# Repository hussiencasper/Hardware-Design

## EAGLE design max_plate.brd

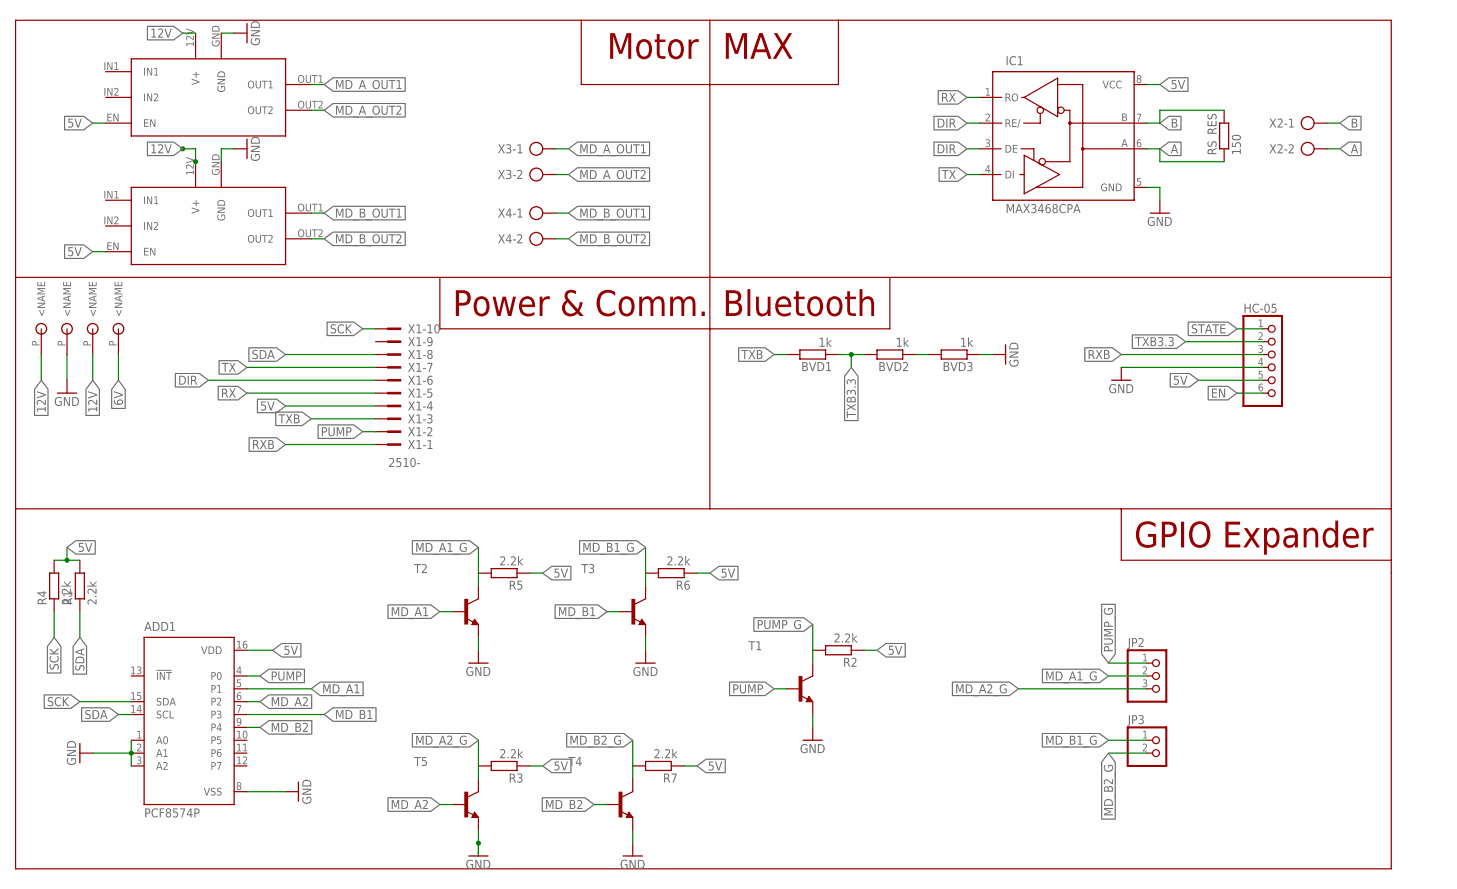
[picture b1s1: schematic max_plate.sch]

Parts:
ADD1: PCF8574P; DIL16
BVD1, BVD2, BVD3: 1k; 0207/10
HC-05: PINHD-1X6; 1X06
IC1: MAX3468CPA; DIL08
JP2: PINHD-1X3; 1X03
JP3: PINHD-1X2; 1X02
R1, R2, R3, R4, R5, R6, R7: 2.2k; 0207/10
RS_RES: 150; 0207/10
T1, T2, T3, T4, T5: -NPN-TO92; TO92
U$1, U$2, U$3, U$4: CU-SPACER
U$5, U$6: L6203-MODULE
X1: 2510-; PAK100/2500-10
X2, X3, X4: AK500/2

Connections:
5V: ADD1.16 (VDD), HC-05.5, IC1.8 (VCC), R1.2, R2.1, R3.1, R4.2, R5.1, R6.1, R7.1, U$5.EN, U$6.EN, X1.4
6V: U$4.P
12V: U$1.P, U$3.P, U$5.12V (V+), U$6.12V (V+)
A: IC1.6 (A), RS_RES.1, X2.2
B: IC1.7 (B), RS_RES.2, X2.1
DIR: IC1.2 (RE/), IC1.3 (DE), X1.6
EN: HC-05.6
GND: ADD1.1 (A0), ADD1.2 (A1), ADD1.3 (A2), ADD1.8 (VSS), BVD3.1, HC-05.4, IC1.5 (GND), T1.1 (E), T2.1 (E), T3.1 (E), T4.1 (E), T5.1 (E), U$2.P, U$5.GND, U$6.GND
MD_A1: ADD1.5 (P1), T2.2 (B)
MD_A1_G: JP2.2, R5.2, T2.3 (C)
MD_A2: ADD1.6 (P2), T5.2 (B)
MD_A2_G: JP2.3, R3.2, T5.3 (C)
MD_A_OUT1: U$5.OUT1, X3.1
MD_A_OUT2: U$5.OUT2, X3.2
MD_B1: ADD1.7 (P3), T3.2 (B)
MD_B1_G: JP3.1, R6.2, T3.3 (C)
MD_B2: ADD1.9 (P4), T4.2 (B)
MD_B2_G: JP3.2, R7.2, T4.3 (C)
MD_B_OUT1: U$6.OUT1, X4.1
MD_B_OUT2: U$6.OUT2, X4.2
unnamed: BVD2.1, BVD3.2
PUMP: ADD1.4 (P0), T1.2 (B), X1.2
PUMP_G: JP2.1, R2.2, T1.3 (C)
RX: IC1.1 (RO), X1.5
RXB: HC-05.3, X1.1
SCK: ADD1.15 (SDA), R4.1, X1.10
SDA: ADD1.14 (SCL), R1.1, X1.8
STATE: HC-05.1
TX: IC1.4 (DI), X1.7
TXB: BVD1.2, X1.3
TXB3.3: BVD1.1, BVD2.2, HC-05.2

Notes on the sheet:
MAX
Motor
Bluetooth
Power & Comm.
GPIO Expander

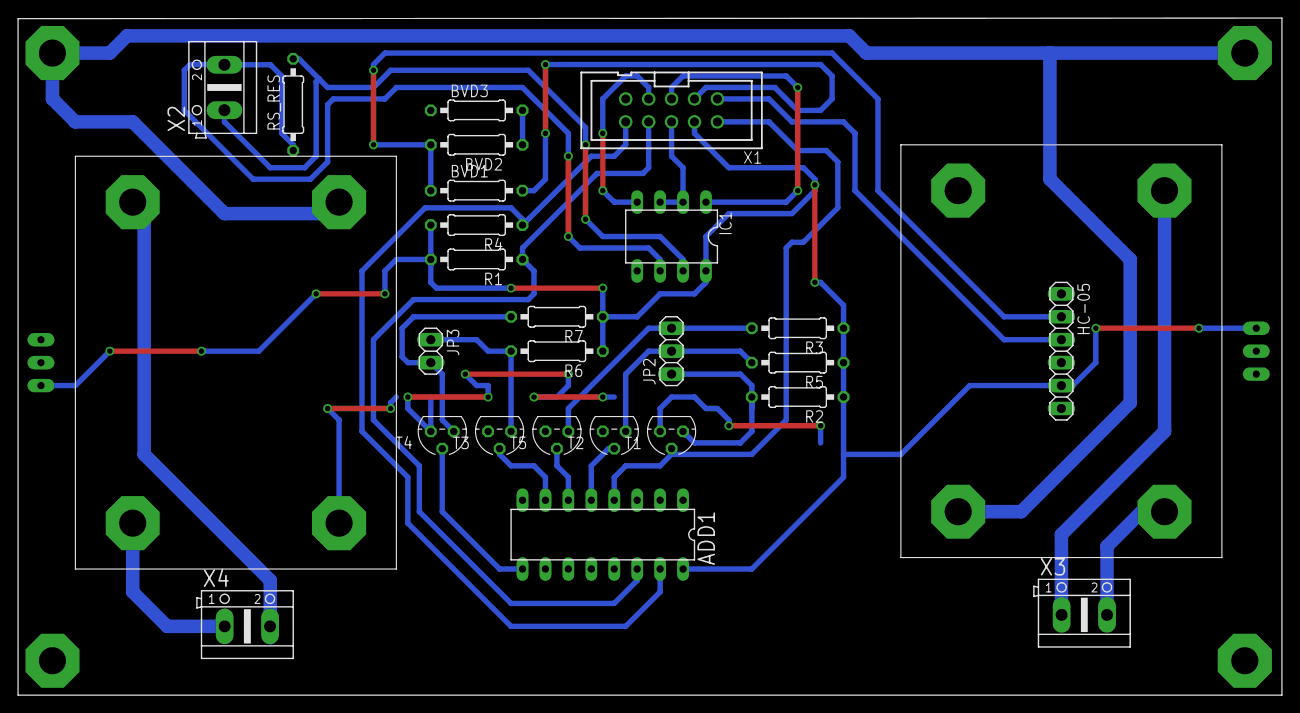
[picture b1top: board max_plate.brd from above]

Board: 2 copper layers, 140.0 x 75.0 mm, 31 parts (0 on the bottom side), 28 nets.

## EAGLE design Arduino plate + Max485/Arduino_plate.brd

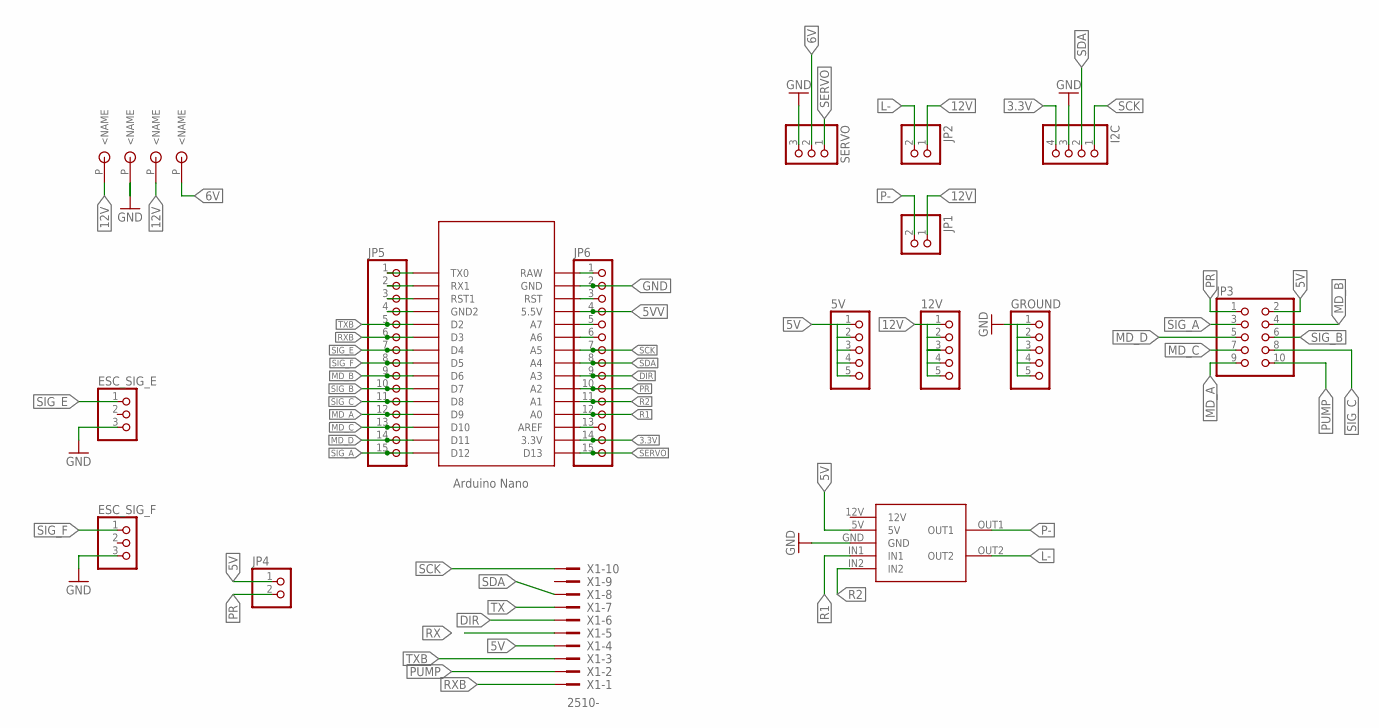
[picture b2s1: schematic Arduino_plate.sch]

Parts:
5V, 12V: PINHD-1X5; 1X05
6V, 12: CU-SPACER
ESC_SIG_E: PINHD-1X3/90; 1X03/90
ESC_SIG_F: PINHD-1X3/90; 1X03/90
GND: CU-SPACER
GROUND: PINHD-1X5; 1X05
I2C: PINHD-1X4/90; 1X04/90
JP1, JP2, JP4: PINHD-1X2/90; 1X02/90
JP3: PINHD-2X5; 2X05
JP5, JP6: PINHD-1X15; 1X15
SERVO: PINHD-1X3/90; 1X03/90
U$1: NANO
U$3: 2-RELAY-MODULE
U$4: CU-SPACER
X1: 2510-; PAK100/2500-10

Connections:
3.3V: I2C.4, JP6.14, U$1.3.3V
5V: 5V.1, 5V.2, 5V.3, 5V.4, 5V.5, JP3.2, JP4.1, U$3.5V, X1.4
5VV: JP6.4, U$1.5V (5.5V)
6V: 6V.P, SERVO.2
12V: 12.P, 12V.1, 12V.2, 12V.3, 12V.4, 12V.5, JP1.1, JP2.1, U$4.P
DIR: JP6.9, U$1.A3, X1.6
GND: ESC_SIG_E.3, ESC_SIG_F.3, GND.P, GROUND.1, GROUND.2, GROUND.3, GROUND.4, GROUND.5, I2C.3, JP6.2, SERVO.3, U$1.GND, U$3.GND
L-: JP2.2, U$3.OUT2
MD_A: JP3.9, JP5.12, U$1.D9
MD_B: JP3.4, JP5.9, U$1.D6
MD_C: JP3.7, JP5.13, U$1.D10
MD_D: JP3.5, JP5.14, U$1.D11
unnamed: JP5.3, U$1.RST1
unnamed: JP5.4, U$1.GND1 (GND2)
unnamed: JP6.1, U$1.RAW
unnamed: JP6.3, U$1.RST
unnamed: JP6.5, U$1.A7
unnamed: JP6.6, U$1.A6
unnamed: JP6.13, U$1.AREF
P-: JP1.2, U$3.OUT1
PR: JP3.1, JP4.2, JP6.10, U$1.A2
PUMP: JP3.10, X1.2
R1: JP6.12, U$1.A0, U$3.IN1
R2: JP6.11, U$1.A1, U$3.IN2
RX: JP5.2, U$1.RX1, X1.5
RXB: JP5.6, U$1.D3, X1.1
SCK: I2C.1, JP6.7, U$1.A5, X1.10
SDA: I2C.2, JP6.8, U$1.A4, X1.8
SERVO: JP6.15, SERVO.1, U$1.D13
SIG_A: JP3.3, JP5.15, U$1.D12
SIG_B: JP3.6, JP5.10, U$1.D7
SIG_C: JP3.8, JP5.11, U$1.D8
SIG_E: ESC_SIG_E.1, JP5.7, U$1.D4
SIG_F: ESC_SIG_F.1, JP5.8, U$1.D5
TX: JP5.1, U$1.TX0, X1.7
TXB: JP5.5, U$1.D2, X1.3

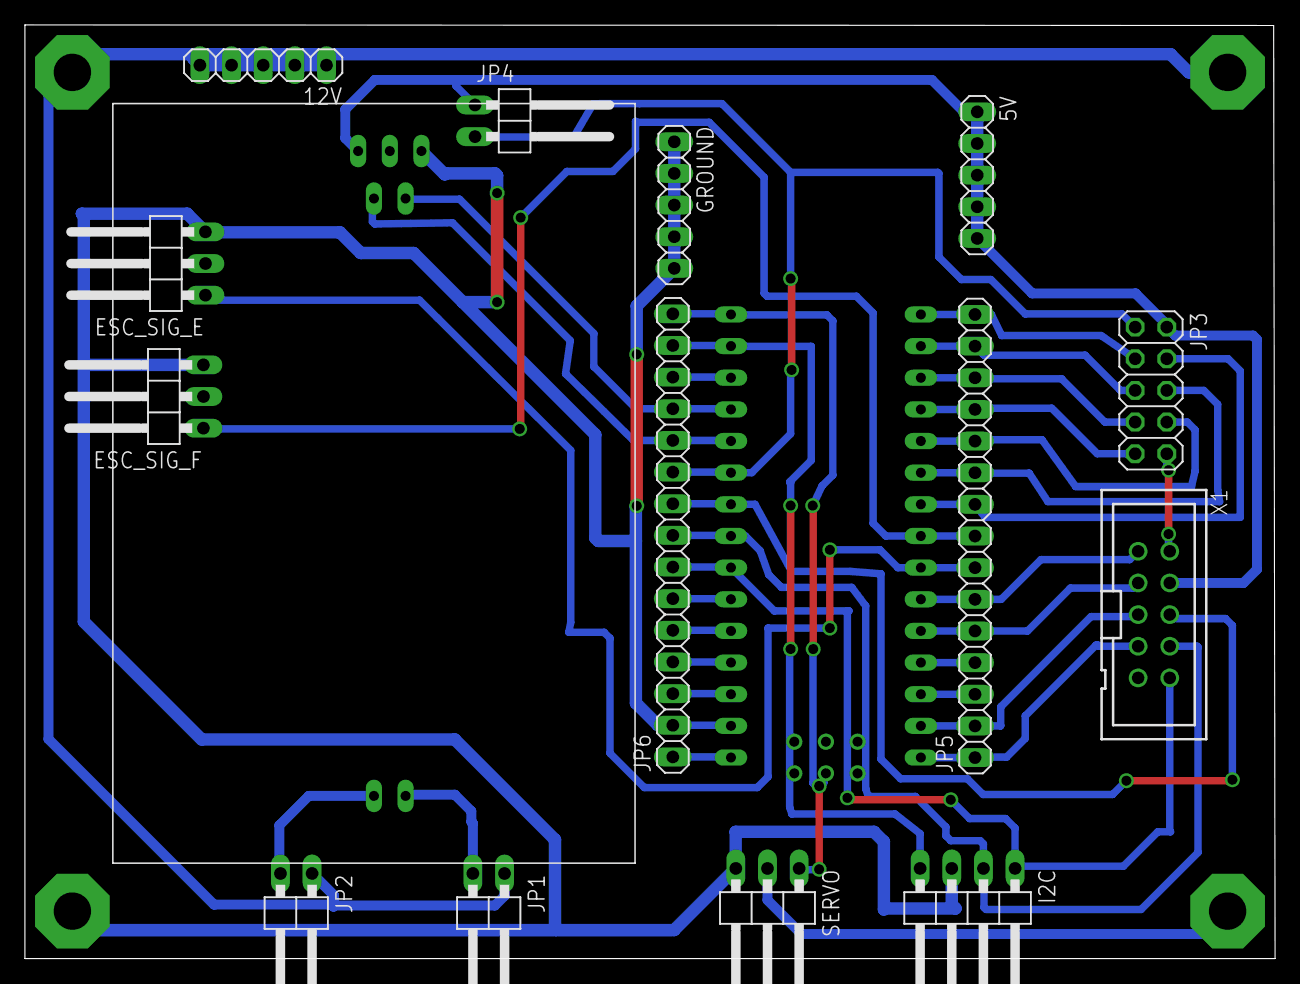
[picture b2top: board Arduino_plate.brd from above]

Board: 2 copper layers, 100.3 x 74.9 mm, 20 parts (0 on the bottom side), 36 nets.

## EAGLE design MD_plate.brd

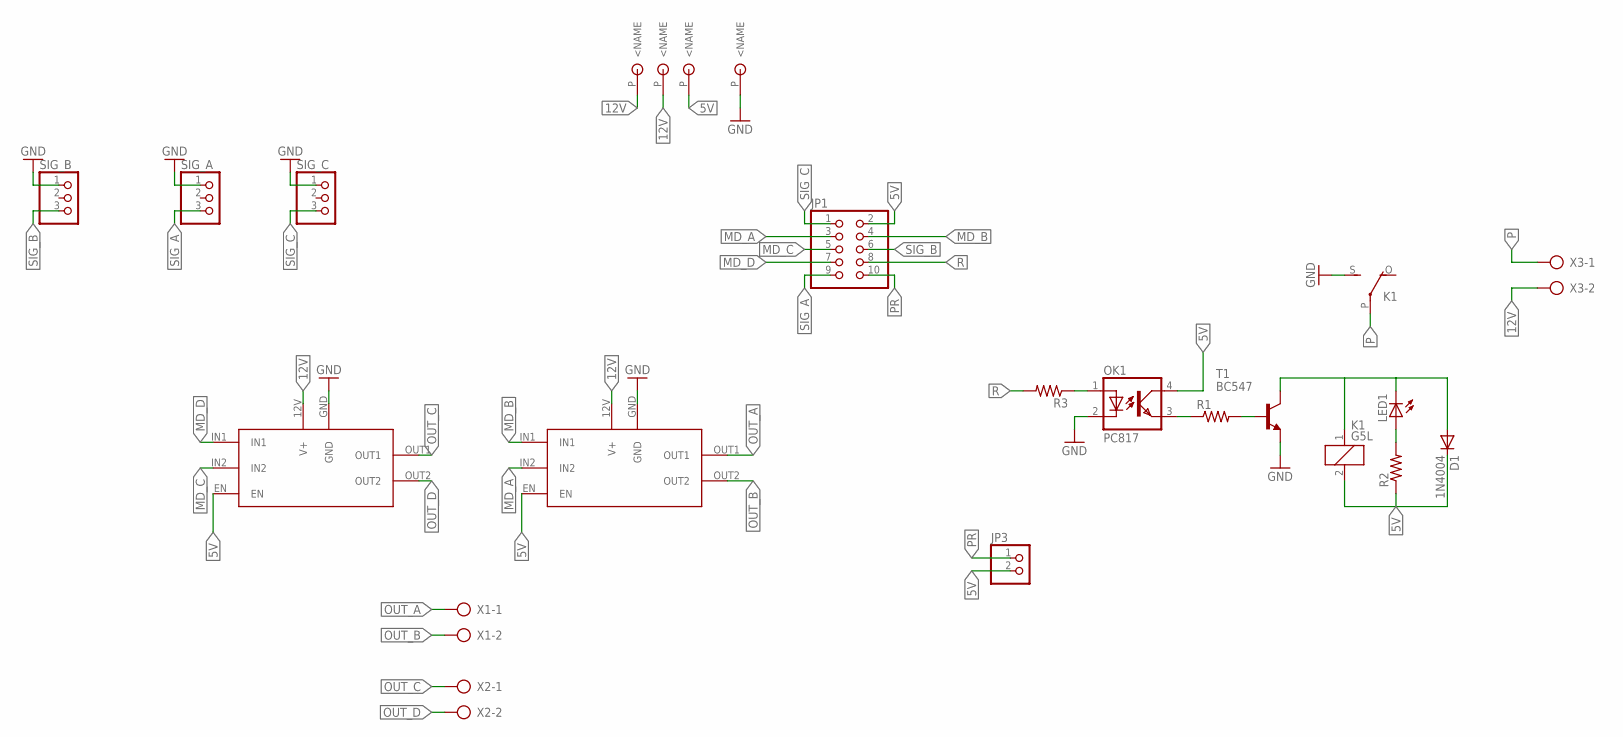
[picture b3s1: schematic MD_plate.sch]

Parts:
6, 12_A, 12_B: CU-SPACER
D1: 1N4004; DO41-10
JP1: PINHD-2X5; 2X05
JP3: PINHD-1X2; 1X02
K1: G5L; G5LE
LED1: LED3MM
OK1: PC817; DIL04
R1, R2, R3: R-US_0204/7; 0204/7
SIG_A: PINHD-1X3/90; 1X03/90
SIG_B: PINHD-1X3/90; 1X03/90
SIG_C: PINHD-1X3/90; 1X03/90
T1: BC547; TO92
U$1, U$2: L6203-MODULE
U$6: CU-SPACER
X1, X2, X3: AK500/2

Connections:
5V: 6.P, D1.C, JP1.2, JP3.2, K1.2, OK1.4 (COL), R2.1, U$1.EN, U$2.EN
12V: 12_A.P, 12_B.P, U$1.12V (V+), U$2.12V (V+), X3.2
GND: K1.S, OK1.2 (C), SIG_A.1, SIG_B.1, SIG_C.1, T1.1 (E), U$1.GND, U$2.GND, U$6.P
MD_A: JP1.3, U$2.IN2
MD_B: JP1.4, U$2.IN1
MD_C: JP1.5, U$1.IN2
MD_D: JP1.7, U$1.IN1
unnamed: OK1.3 (EMIT), R1.1
unnamed: R1.2, T1.2 (B)
unnamed: LED1.A, R2.2
unnamed: OK1.1 (A), R3.1
unnamed: D1.A, K1.1, LED1.K (C), T1.3 (C)
OUT_A: U$2.OUT1, X1.1
OUT_B: U$2.OUT2, X1.2
OUT_C: U$1.OUT1, X2.1
OUT_D: U$1.OUT2, X2.2
P: K1.P, X3.1
PR: JP1.10, JP3.1
R: JP1.8, R3.2
SIG_A: JP1.9, SIG_A.3
SIG_B: JP1.6, SIG_B.3
SIG_C: JP1.1, SIG_C.3

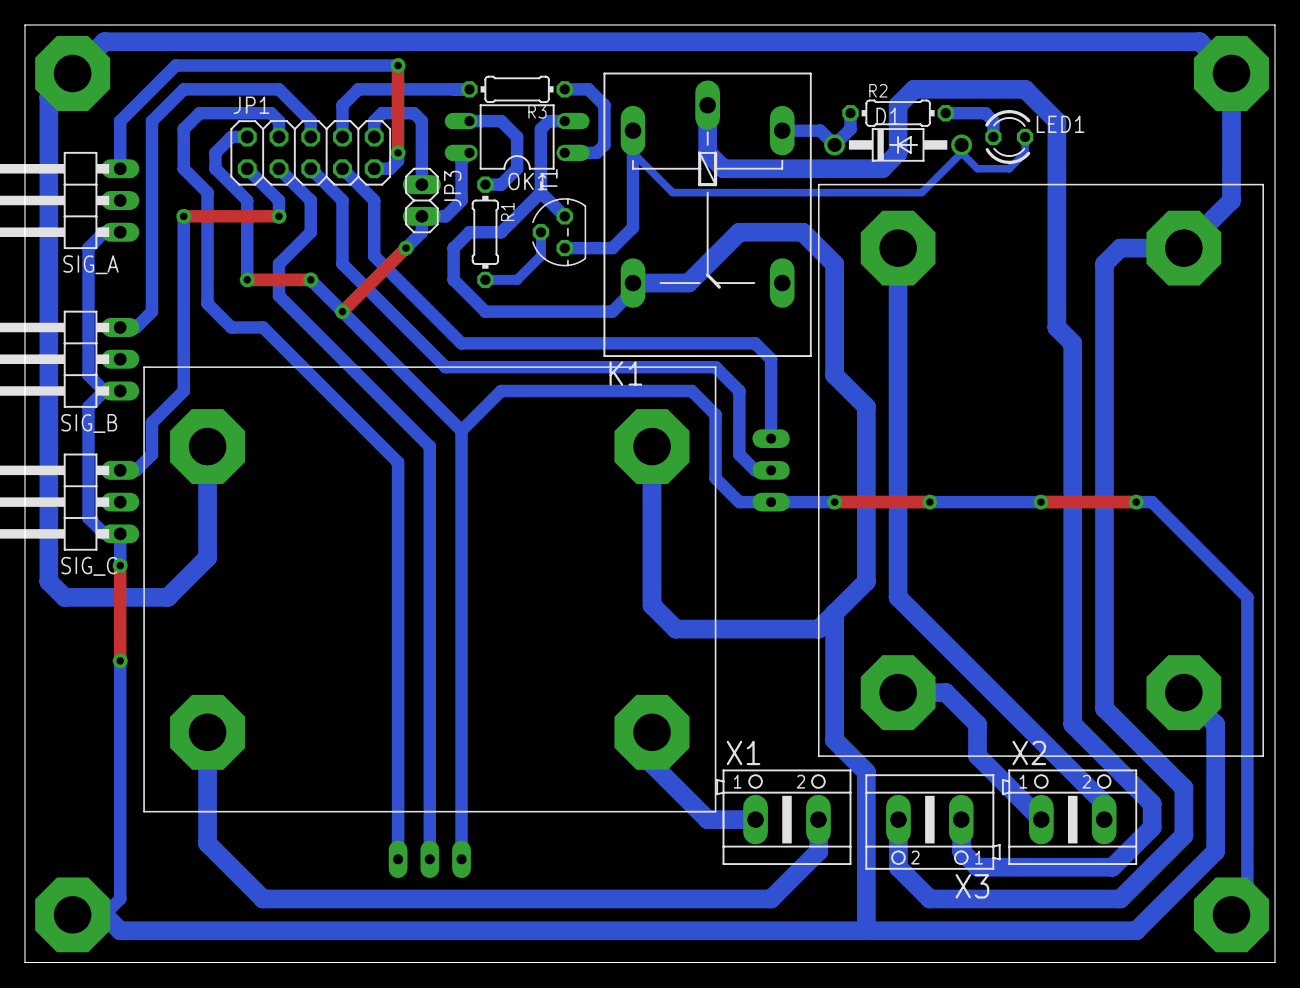
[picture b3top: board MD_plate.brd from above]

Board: 2 copper layers, 100.0 x 75.0 mm, 22 parts (0 on the bottom side), 22 nets.

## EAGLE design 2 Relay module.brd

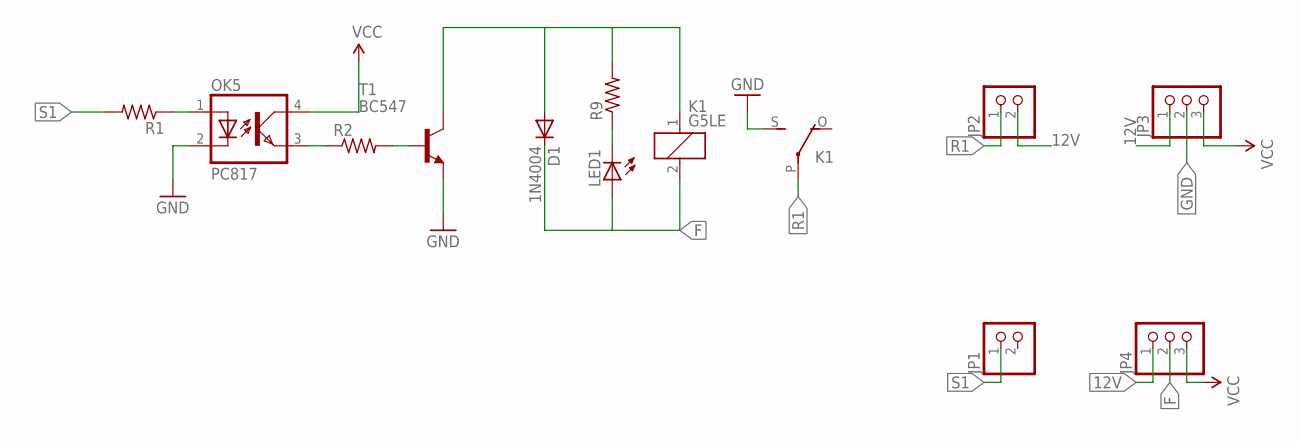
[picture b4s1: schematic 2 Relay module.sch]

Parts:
D1: 1N4004; DO41-10
JP1, JP2: PINHD-1X2; 1X02
JP3, JP4: PINHD-1X3; 1X03
K1: G5LE
LED1: LED3MM
OK5: PC817; DIL04
R1, R2, R9: R-US_0204/7; 0204/7
T1: BC547; TO92

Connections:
12V: JP2.2, JP3.1, JP4.1
F: D1.C, JP4.2, K1.2, LED1.A
GND: JP3.2, K1.S, OK5.2 (C), T1.1 (E)
unnamed: LED1.K (C), R9.1
unnamed: OK5.3 (EMIT), R2.1
unnamed: OK5.1 (A), R1.1
unnamed: R2.2, T1.2 (B)
unnamed: D1.A, K1.1, R9.2, T1.3 (C)
R1: JP2.1, K1.P
S1: JP1.1, R1.2
VCC: JP3.3, JP4.3, OK5.4 (COL)

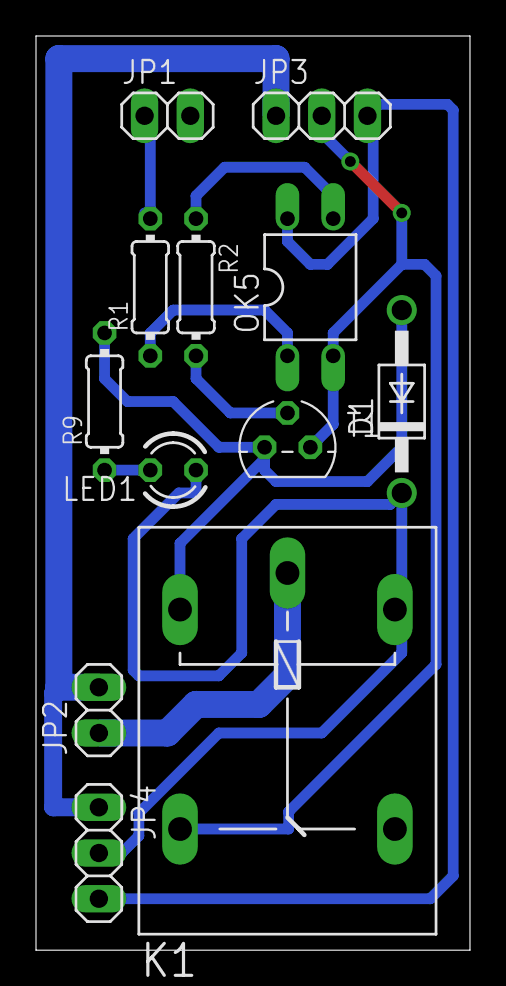
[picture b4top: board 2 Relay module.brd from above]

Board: 2 copper layers, 24.1 x 50.8 mm, 12 parts (0 on the bottom side), 11 nets.

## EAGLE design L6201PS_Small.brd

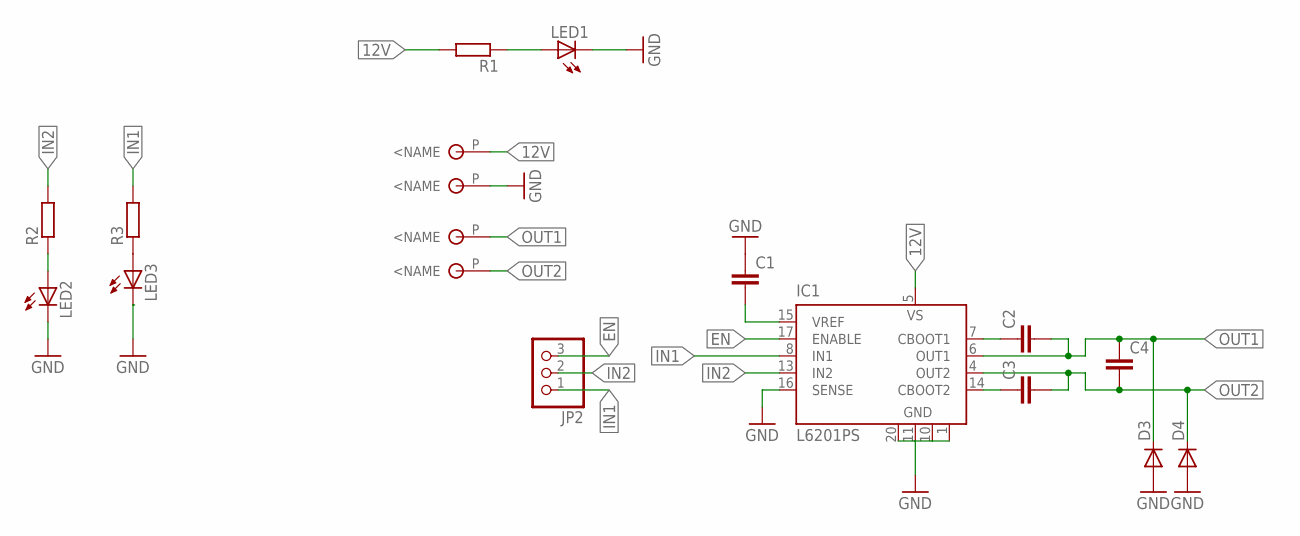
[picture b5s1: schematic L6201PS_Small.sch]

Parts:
C1, C2, C3, C4: C-EUC0603; C0603
D3, D4: DIODE-DO214AC; DO214AC
IC1: L6201PS; POWERSO-20
JP2: PINHD-1X3; 1X03
LED1, LED2, LED3: LEDSML0603; SML0603
R1, R2, R3: R-EU_R0603; R0603
U$1, U$2, U$3, U$4: CU-SPACER

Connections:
12V: IC1.5 (VS), R1.2, U$2.P
EN: IC1.17 (ENABLE), JP2.3
GND: C1.1, D3.A, D4.A, IC1.1 (GND), IC1.10 (GND), IC1.11 (GND), IC1.16 (SENSE), IC1.20 (GND), LED1.C, LED2.C, LED3.C, U$1.P
IN1: IC1.8 (IN1), JP2.1, R3.2
IN2: IC1.13 (IN2), JP2.2, R2.2
unnamed: LED3.A, R3.1
unnamed: LED1.A, R1.1
unnamed: C1.2, IC1.15 (VREF)
unnamed: C2.1, IC1.7 (CBOOT1)
unnamed: LED2.A, R2.1
unnamed: C3.1, IC1.14 (CBOOT2)
OUT1: C2.2, C4.1, D3.C, IC1.6 (OUT1), U$3.P
OUT2: C3.2, C4.2, D4.C, IC1.4 (OUT2), U$4.P

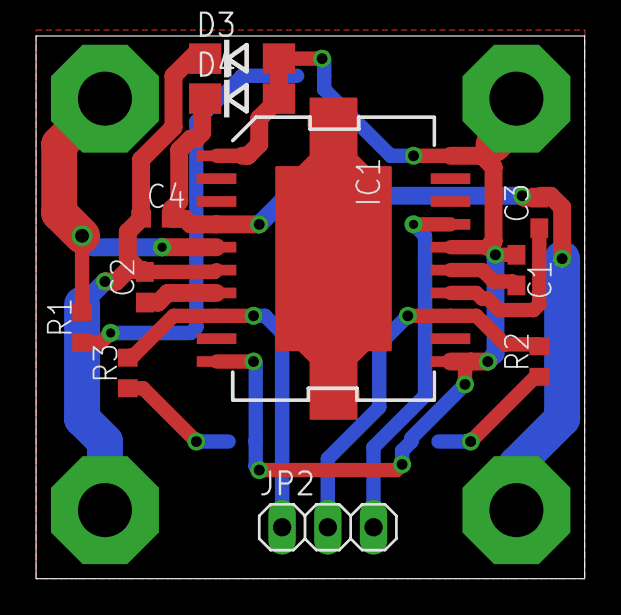
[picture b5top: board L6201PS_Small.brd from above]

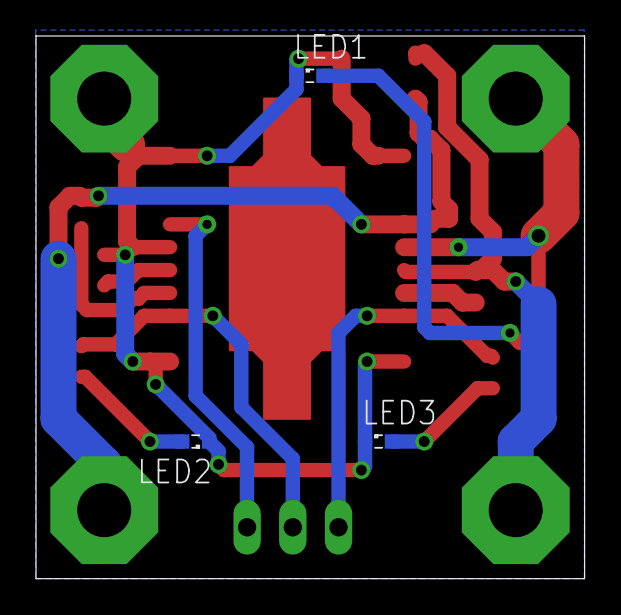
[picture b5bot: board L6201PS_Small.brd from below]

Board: 2 copper layers, 30.5 x 30.1 mm, 18 parts (3 on the bottom side), 13 nets.

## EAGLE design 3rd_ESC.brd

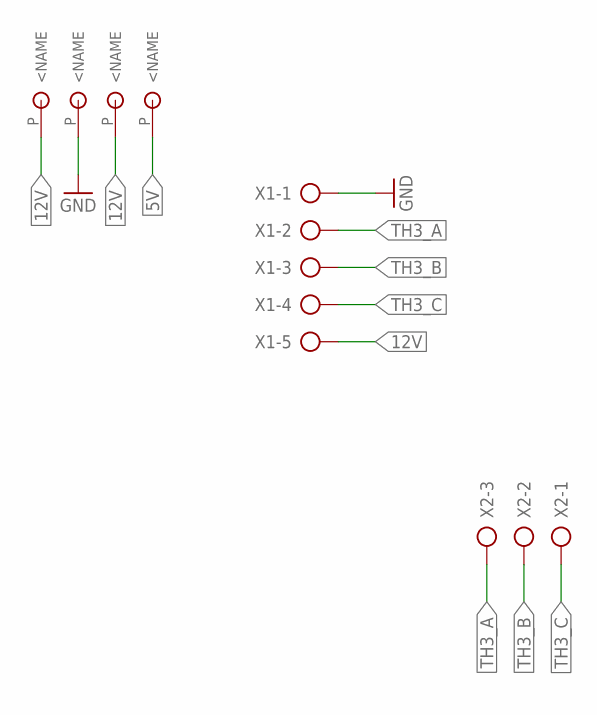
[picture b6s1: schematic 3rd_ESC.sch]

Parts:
U$1, U$2, U$3, U$4: CU-SPACER
X1: AK500/5
X2: AK500/3

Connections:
5V: U$4.P
12V: U$1.P, U$3.P, X1.5
GND: U$2.P, X1.1
TH3_A: X1.2, X2.3
TH3_B: X1.3, X2.2
TH3_C: X1.4, X2.1

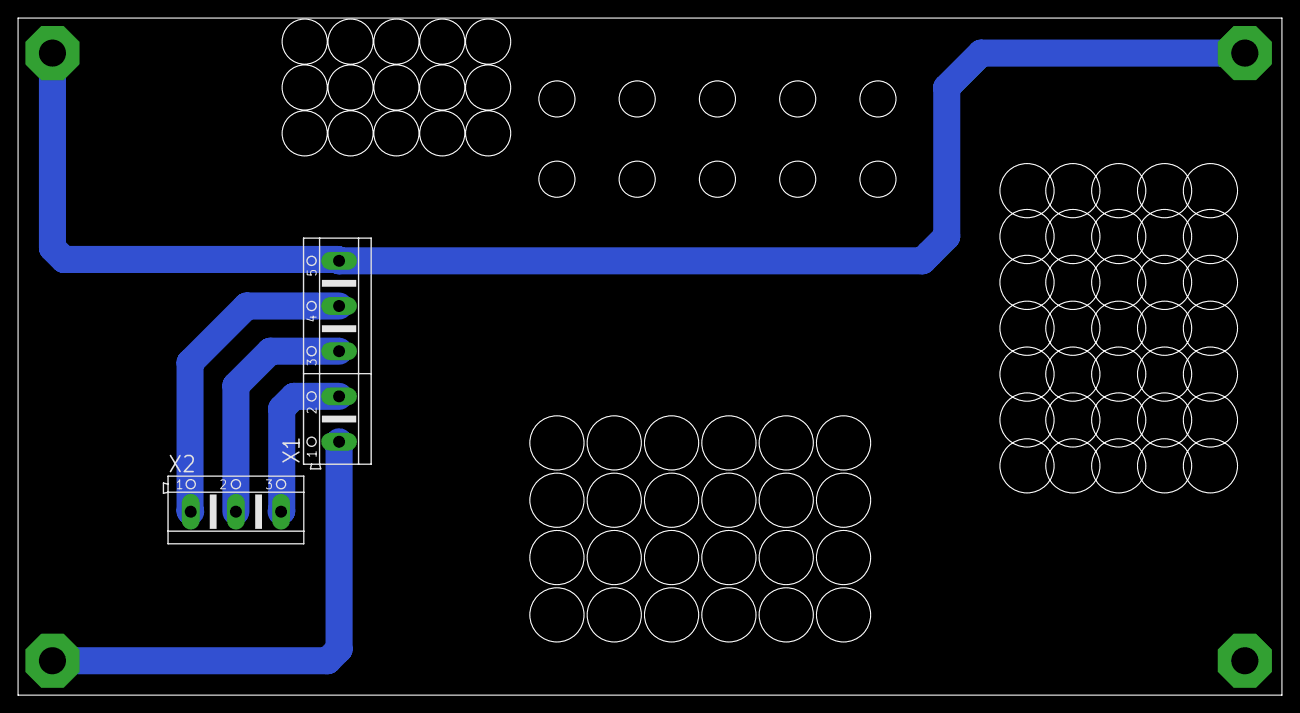
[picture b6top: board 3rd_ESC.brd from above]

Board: 2 copper layers, 140.0 x 75.0 mm, 6 parts (0 on the bottom side), 5 nets.

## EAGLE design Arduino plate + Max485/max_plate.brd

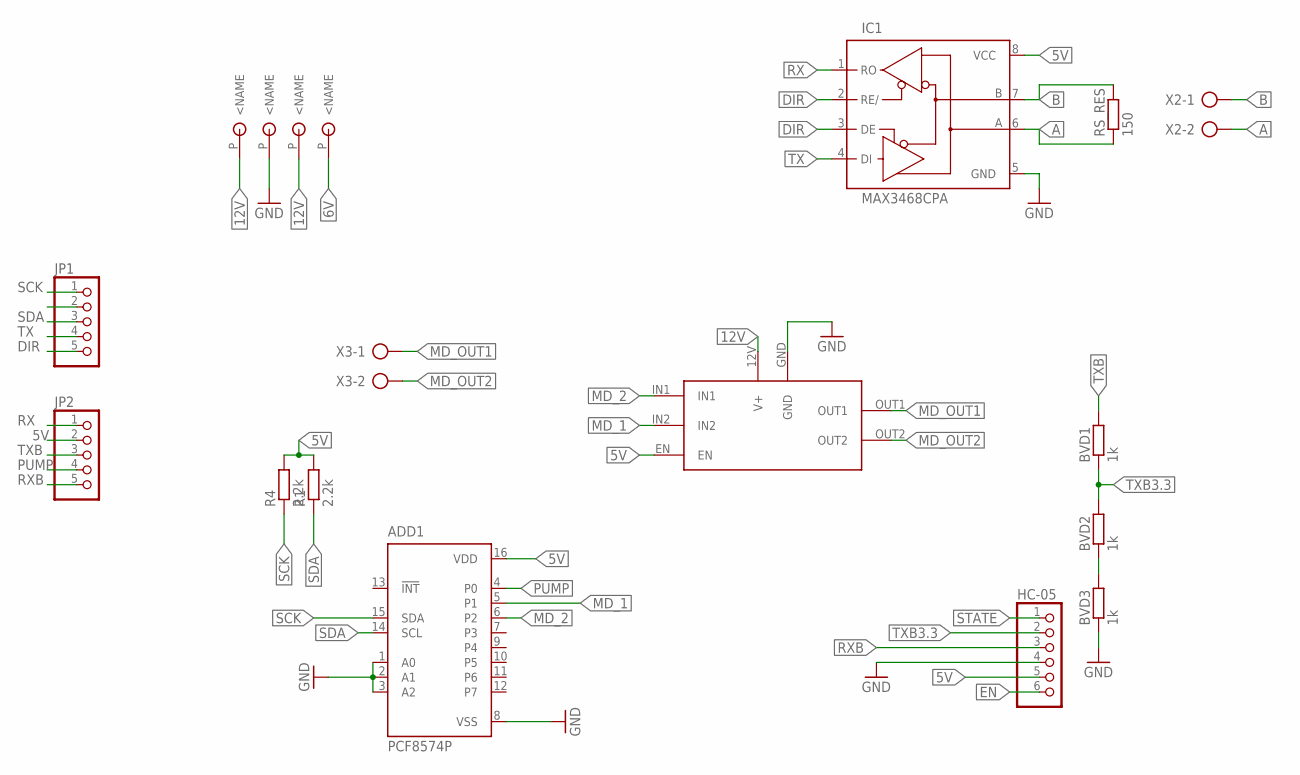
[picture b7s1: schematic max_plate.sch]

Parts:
ADD1: PCF8574P; DIL16
BVD1, BVD2, BVD3: 1k; 0207/10
HC-05: PINHD-1X6; 1X06
IC1: MAX3468CPA; DIL08
JP1, JP2: PINHD-1X5; 1X05
R1, R4: 2.2k; 0207/10
RS_RES: 150; 0207/10
U$1, U$2, U$3, U$4: CU-SPACER
U$5: L6203-MODULE
X2, X3: AK500/2

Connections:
5V: ADD1.16 (VDD), HC-05.5, IC1.8 (VCC), JP2.2, R1.2, R4.2, U$5.EN
6V: U$4.P
12V: U$1.P, U$3.P, U$5.12V (V+)
A: IC1.6 (A), RS_RES.1, X2.2
B: IC1.7 (B), RS_RES.2, X2.1
DIR: IC1.2 (RE/), IC1.3 (DE), JP1.5
EN: HC-05.6
GND: ADD1.1 (A0), ADD1.2 (A1), ADD1.3 (A2), ADD1.8 (VSS), BVD3.1, HC-05.4, IC1.5 (GND), U$2.P, U$5.GND
MD_1: ADD1.5 (P1), U$5.IN2
MD_2: ADD1.6 (P2), U$5.IN1
MD_OUT1: U$5.OUT1, X3.1
MD_OUT2: U$5.OUT2, X3.2
unnamed: BVD2.1, BVD3.2
PUMP: ADD1.4 (P0), JP2.4
RX: IC1.1 (RO), JP2.1
RXB: HC-05.3, JP2.5
SCK: ADD1.15 (SDA), JP1.1, R4.1
SDA: ADD1.14 (SCL), JP1.3, R1.1
STATE: HC-05.1
TX: IC1.4 (DI), JP1.4
TXB: BVD1.2, JP2.3
TXB3.3: BVD1.1, BVD2.2, HC-05.2

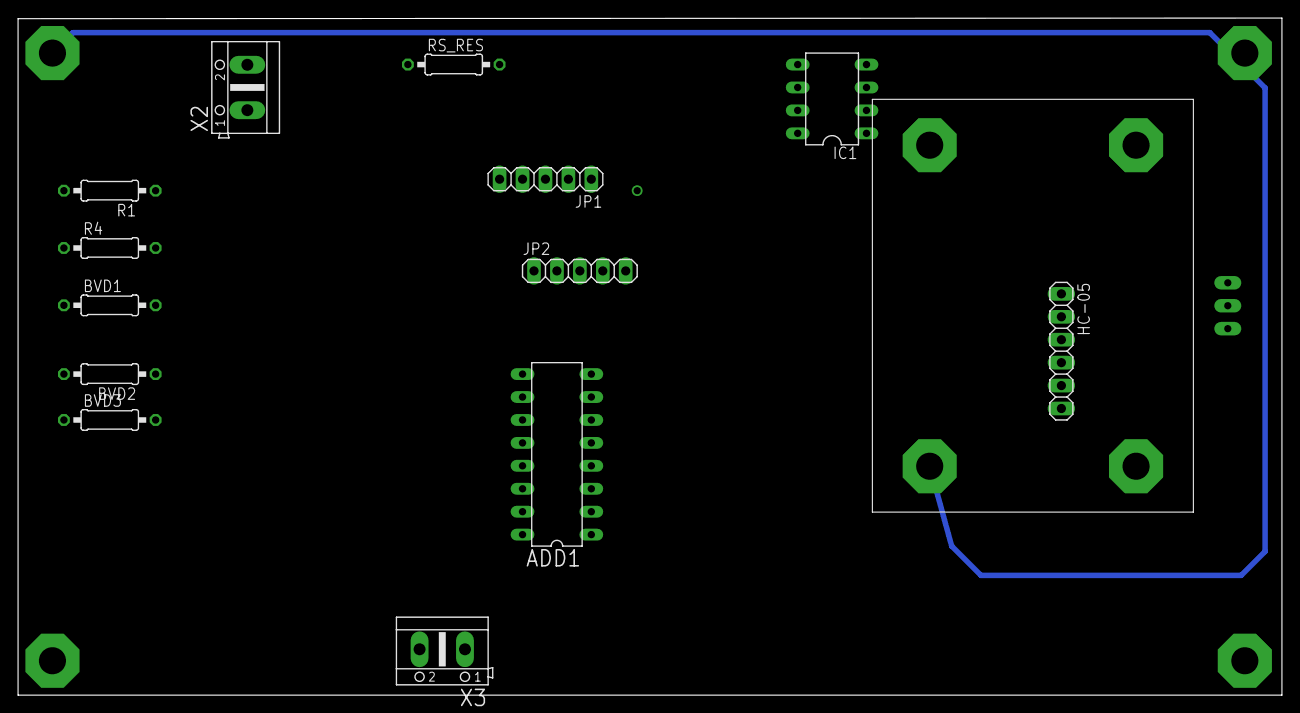
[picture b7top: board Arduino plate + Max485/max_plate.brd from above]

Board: 2 copper layers, 140.0 x 75.0 mm, 18 parts (0 on the bottom side), 19 nets.

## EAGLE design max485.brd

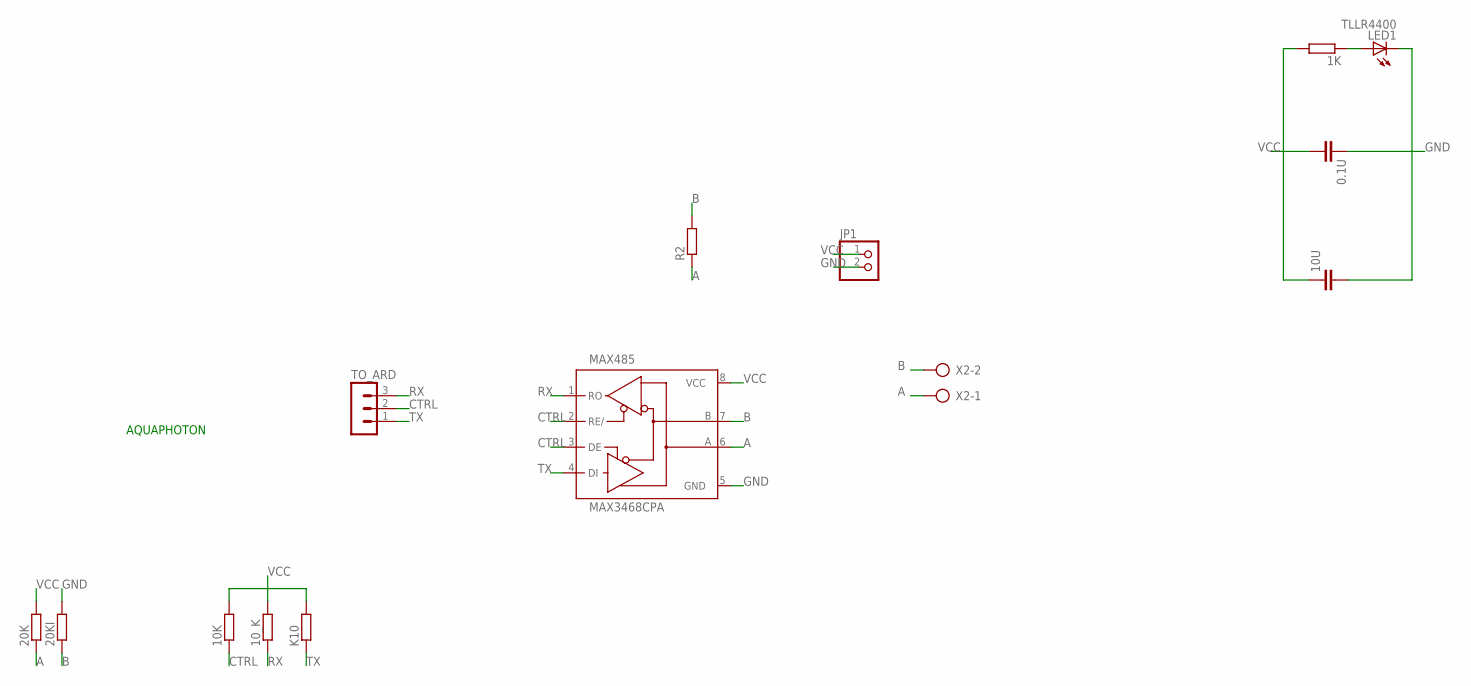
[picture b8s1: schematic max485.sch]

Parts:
0.1U, 10U: C5/2.5; C5B2.5
1K, 10K, 10_K, 20K, 20KI: R-EU_0207/10; 0207/10
JP1: PINHD-1X2; 1X02
K10: R-EU_0207/10; 0207/10
LED1: TLLR4400; LED3MM
MAX485: MAX3468CPA; DIL08
R2: R-EU_0207/10; 0207/10
TO_ARD: MA03-1
X2: AK500/2-H

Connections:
A: 20K.1, MAX485.6 (A), R2.1, X2.1
B: 20KI.1, MAX485.7 (B), R2.2, X2.2
CTRL: 10K.1, MAX485.2 (RE/), MAX485.3 (DE), TO_ARD.2
GND: 0.1U.1, 10U.2, 20KI.2, JP1.2, LED1.K (C), MAX485.5 (GND)
unnamed: 1K.1, LED1.A
RX: 10_K.1, MAX485.1 (RO), TO_ARD.3
TX: K10.1, MAX485.4 (DI), TO_ARD.1
VCC: 0.1U.2, 1K.2, 10K.2, 10U.1, 10_K.2, 20K.2, JP1.1, K10.2, MAX485.8 (VCC)

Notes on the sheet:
AQUAPHOTON

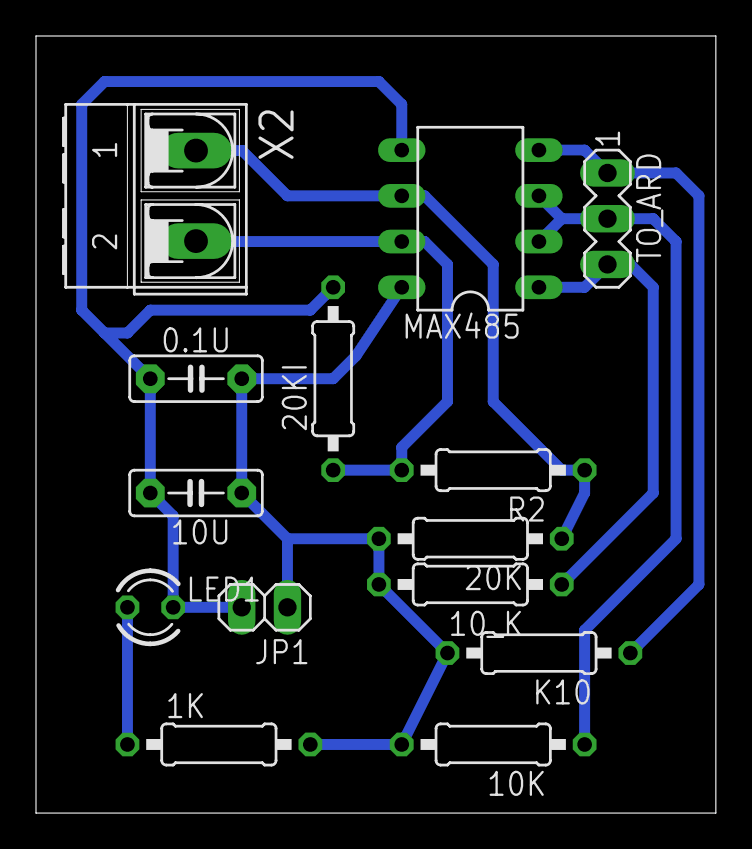
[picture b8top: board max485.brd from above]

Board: 2 copper layers, 37.8 x 43.2 mm, 14 parts (0 on the bottom side), 8 nets.

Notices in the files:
parts and their libraries:
SparkFun-Aesthetics: Licensing: Creative Commons ShareAlike 4.0 International - https://creativecommons.org/licenses/by-sa/4.0
